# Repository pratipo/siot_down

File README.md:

# siot_down
workshop and installation in barcelona, by adi-fad + hangar

:)

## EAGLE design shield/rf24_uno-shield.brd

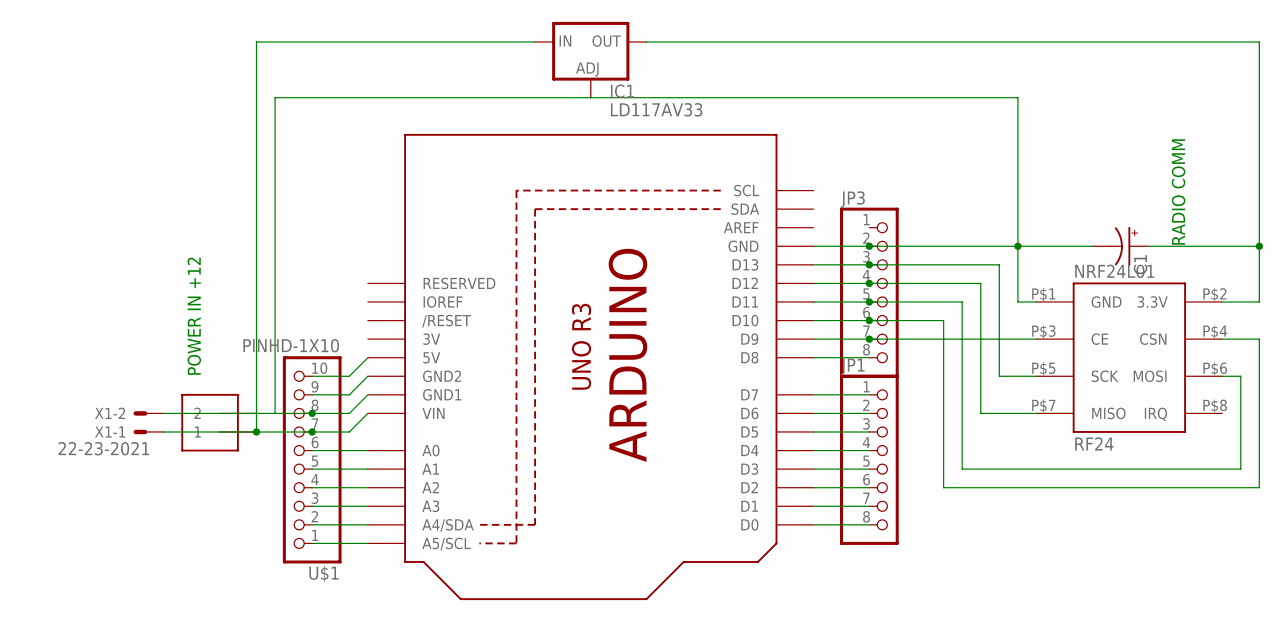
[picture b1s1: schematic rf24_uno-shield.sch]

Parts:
+12V: 1X2-3.5MM
C1: CPOL-USE2-5; E2-5
IC1: LD117AV33; TO220L1
JP1, JP3: PINHD-1X8BIG; 1X08-BIG
NRF24L01: RF24; 4X2HEADER
U1: ARDUINOR3-DIMENSION; ARDUINOR3
U$1: PINHD-1X10; 1X10-BIG
X1: 22-23-2021

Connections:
3V: U1.3V
unnamed: U1.A0, U$1.6
unnamed: C1.+, IC1.2 (OUT), NRF24L01.P$2 (3.3V)
unnamed: +12V.2, C1.-, IC1.1 (ADJ), JP3.2, NRF24L01.P$1 (GND), U1.GND, U1.GND1, U$1.8, X1.2
unnamed: JP3.3, NRF24L01.P$5 (SCK), U1.D13
unnamed: JP3.7, NRF24L01.P$3 (CE), U1.D9
unnamed: JP3.4, NRF24L01.P$7 (MISO), U1.D12
unnamed: JP3.5, NRF24L01.P$6 (MOSI), U1.D11
unnamed: JP3.6, NRF24L01.P$4 (CSN), U1.D10
unnamed: JP1.8, U1.D0
unnamed: U1.A1, U$1.5
unnamed: +12V.1, IC1.3 (IN), U1.VIN, U$1.7, X1.1
unnamed: JP3.8, U1.D8
unnamed: U1.GND2, U$1.9
unnamed: U1.5V, U$1.10
unnamed: U1.A2, U$1.4
unnamed: U1.A3, U$1.3
unnamed: U1.A4 (A4/SDA), U$1.2
unnamed: U1.A5 (A5/SCL), U$1.1
unnamed: JP1.7, U1.D1
unnamed: JP1.6, U1.D2
unnamed: JP1.5, U1.D3
unnamed: JP1.4, U1.D4
unnamed: JP1.3, U1.D5
unnamed: JP1.2, U1.D6
unnamed: JP1.1, U1.D7

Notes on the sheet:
POWER IN +12
RADIO COMM

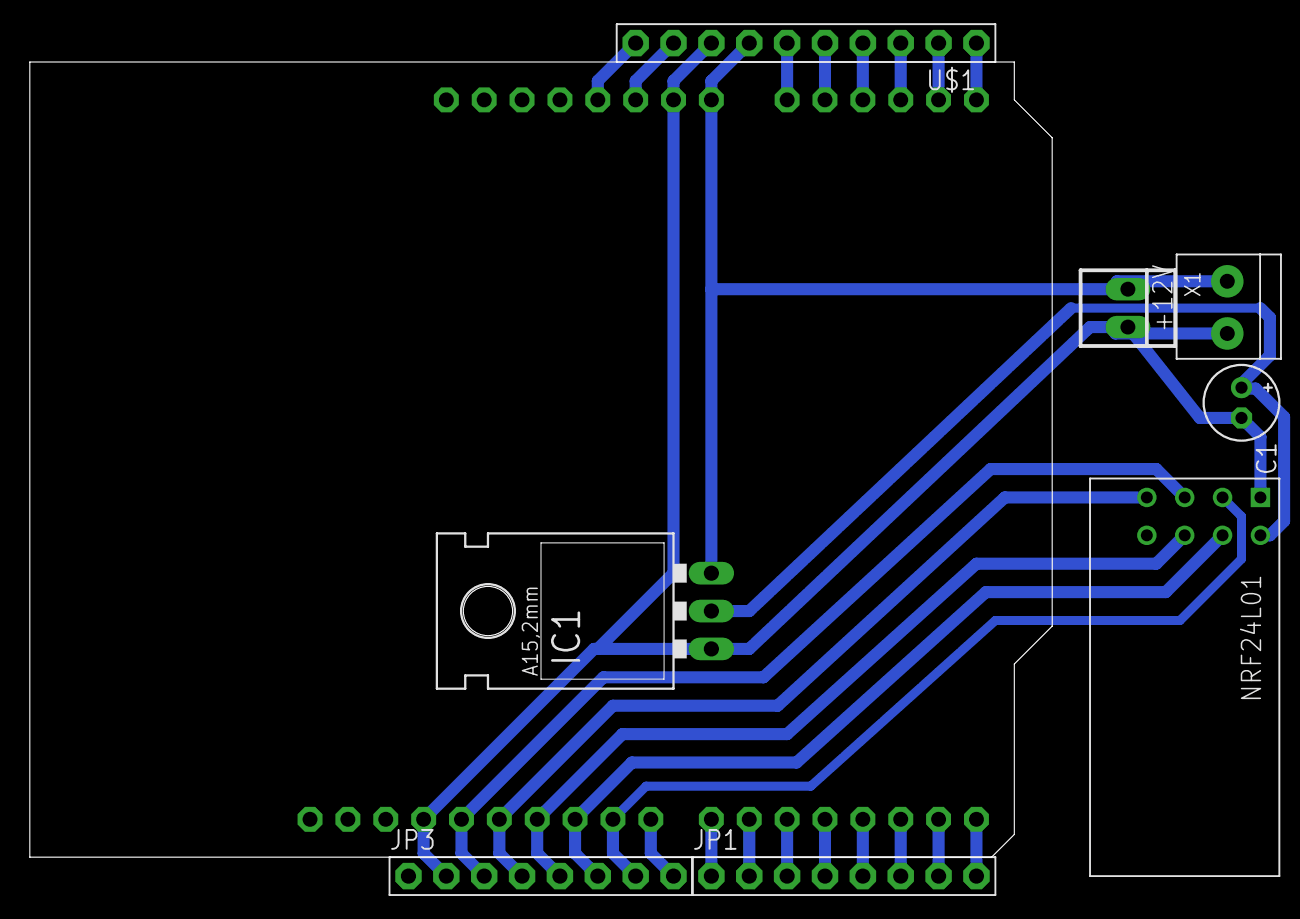
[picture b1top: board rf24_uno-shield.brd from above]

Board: 2 copper layers, 9 parts (1 on the bottom side), 25 nets.

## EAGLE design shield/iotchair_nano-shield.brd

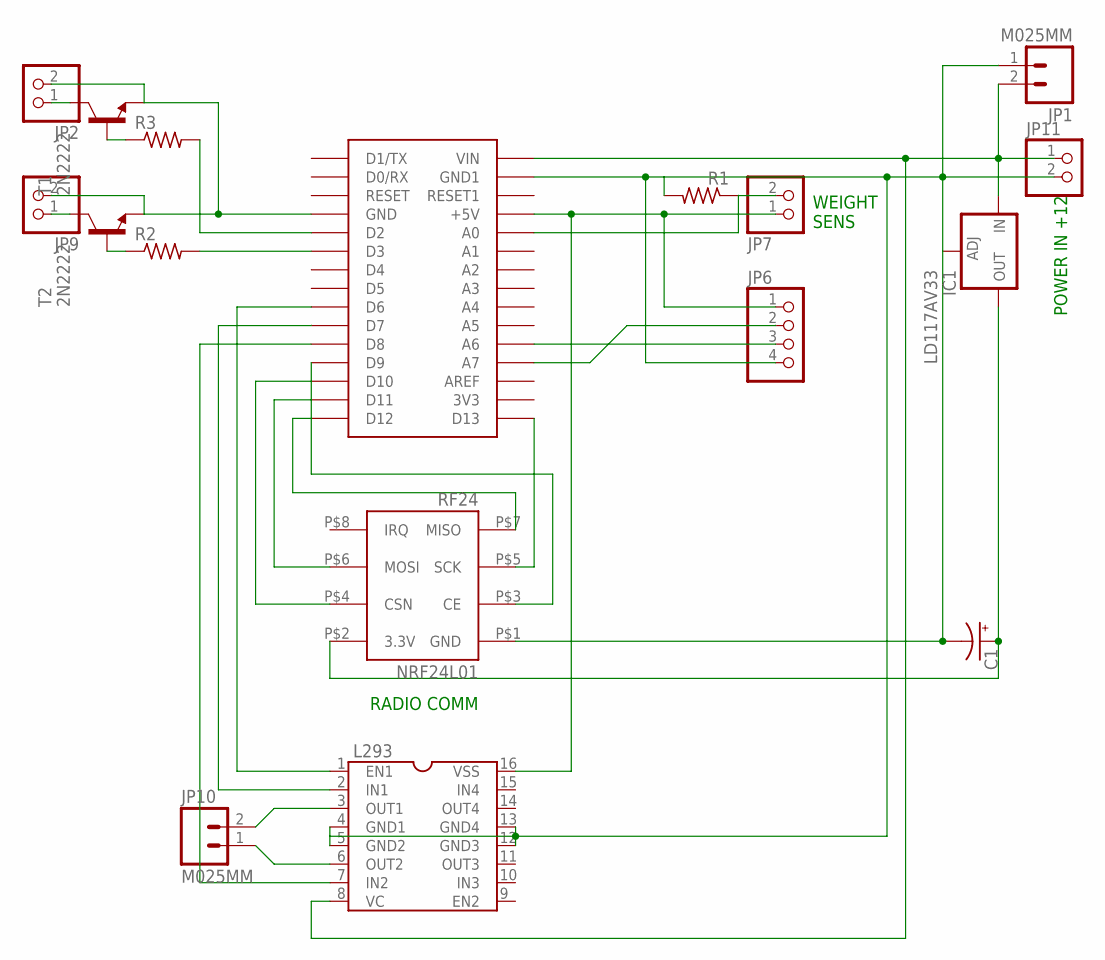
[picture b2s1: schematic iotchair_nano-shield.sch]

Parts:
C1: CPOL-USTT2D6L; TT2D6L
IC1: LD117AV33; TO220L1
JP1, JP10: M025MM; SCREWTERMINAL-5MM-2
JP2, JP7, JP9, JP11: PINHD-1X2; 1X02
JP6: PINHD-1X4; 1X04
L293: DIL16
NRF24L01: RF24; 4X2HEADER
R1, R2, R3: R-US_0204/5; 0204/5
T1, T2: 2N2222; TO92-EBC-OVAL
U$1: ARDUINONANO; PDIP-32

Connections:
unnamed: L293.2 (IN1), U$1.D7
unnamed: C1.+, IC1.2 (OUT), NRF24L01.P$2 (3.3V)
unnamed: JP9.1, T2.C
unnamed: JP6.3, U$1.A6
unnamed: JP7.2, R1.1, U$1.A0
unnamed: IC1.3 (IN), JP1.2, JP11.1, L293.8 (VC), U$1.VIN
unnamed: JP6.2, U$1.A7
unnamed: JP10.1, L293.6 (OUT2)
unnamed: NRF24L01.P$5 (SCK), U$1.D13
unnamed: NRF24L01.P$7 (MISO), U$1.D12
unnamed: NRF24L01.P$6 (MOSI), U$1.D11
unnamed: NRF24L01.P$4 (CSN), U$1.D10
unnamed: NRF24L01.P$3 (CE), U$1.D9
unnamed: L293.1 (EN1), U$1.D6
unnamed: C1.-, IC1.1 (ADJ), JP1.1, JP6.4, JP11.2, L293.4 (GND1), L293.5 (GND2), L293.12 (GND3), L293.13 (GND4), NRF24L01.P$1 (GND), R1.2, U$1.GND1
unnamed: R2.2, U$1.D3
unnamed: L293.7 (IN2), U$1.D8
unnamed: R3.1, T1.B
unnamed: JP2.1, T1.C
unnamed: JP2.2, JP9.2, T1.E, T2.E, U$1.GND
unnamed: R3.2, U$1.D2
unnamed: JP6.1, JP7.1, L293.16 (VSS), U$1.+5V
unnamed: R2.1, T2.B
unnamed: JP10.2, L293.3 (OUT1)

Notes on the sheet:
POWER IN +12
RADIO COMM
WEIGHT SENS

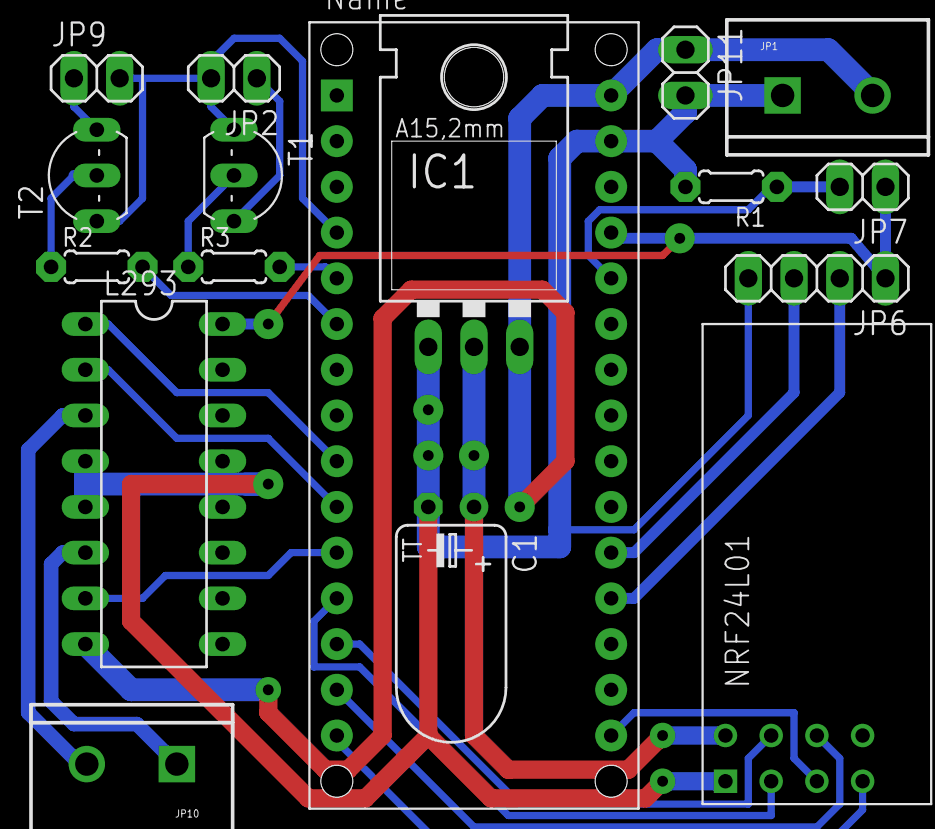
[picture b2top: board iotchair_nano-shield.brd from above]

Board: 2 copper layers, 17 parts (0 on the bottom side), 24 nets.

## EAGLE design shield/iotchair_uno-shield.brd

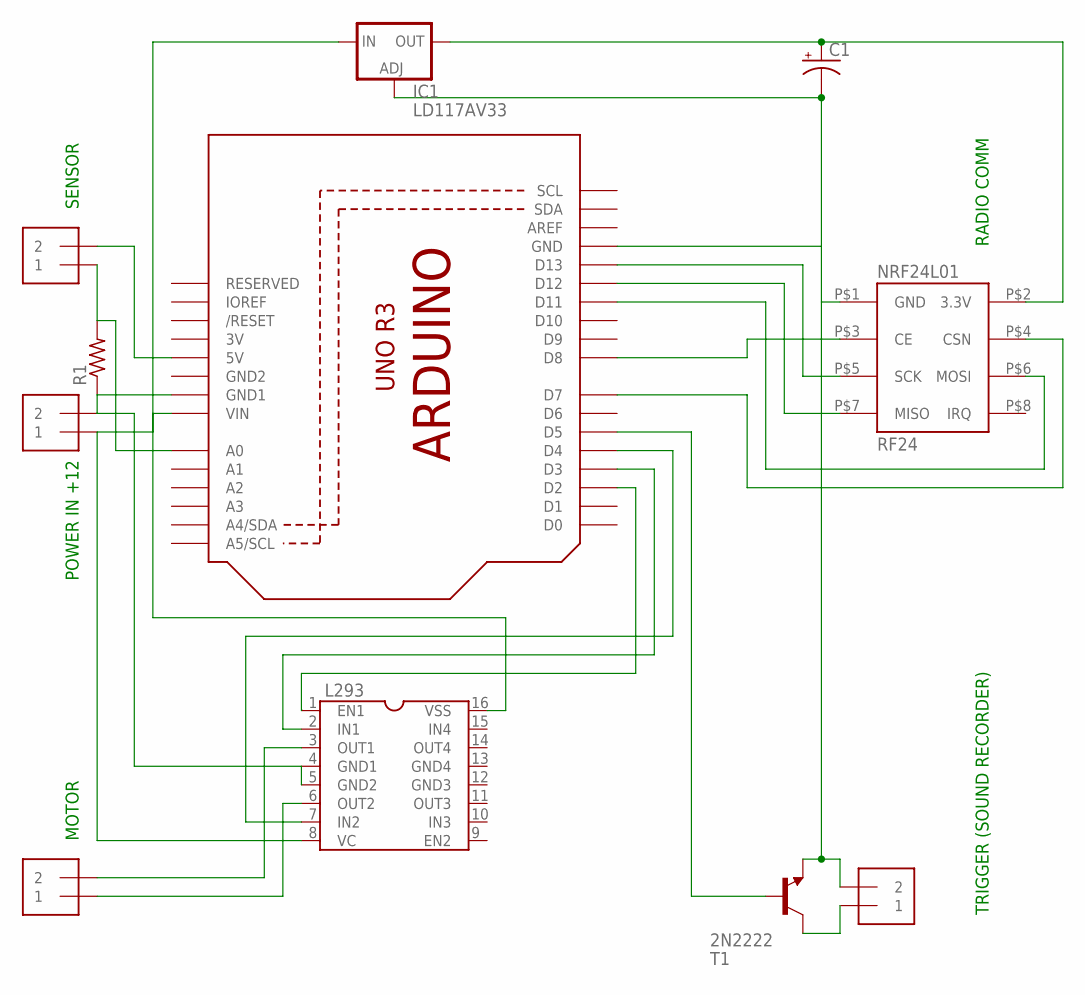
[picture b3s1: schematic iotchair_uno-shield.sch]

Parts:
+12V: 1X2-3.5MM
A_SENS: 1X2-3.5MM
C1: CPOL-USE2-5; E2-5
IC1: LD117AV33; TO220L1
L293: DIL16
MOTOR: 1X2-3.5MM
NRF24L01: RF24; 4X2HEADER
R1: R-US_0207/10; 0207/10
T1: 2N2222; TO92-EBC-OVAL
TRIGGER: 1X2-3.5MM
U1: ARDUINOR3-DIMENSION; ARDUINOR3

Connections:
3V: U1.3V
GND2: U1.GND2
unnamed: A_SENS.2, IC1.3 (IN), L293.16 (VSS), U1.5V
unnamed: C1.+, IC1.2 (OUT), NRF24L01.P$2 (3.3V)
unnamed: C1.-, IC1.1 (ADJ), NRF24L01.P$1 (GND), T1.E, TRIGGER.2, U1.GND
unnamed: NRF24L01.P$5 (SCK), U1.D13
unnamed: NRF24L01.P$3 (CE), U1.D8
unnamed: NRF24L01.P$7 (MISO), U1.D12
unnamed: NRF24L01.P$6 (MOSI), U1.D11
unnamed: NRF24L01.P$4 (CSN), U1.D7
unnamed: A_SENS.1, R1.2, U1.A0
unnamed: L293.6 (OUT2), MOTOR.1
unnamed: +12V.2, L293.4 (GND1), L293.5 (GND2), R1.1, U1.GND1
unnamed: +12V.1, L293.8 (VC), U1.VIN
unnamed: L293.3 (OUT1), MOTOR.2
unnamed: L293.1 (EN1), U1.D2
unnamed: L293.2 (IN1), U1.D3
unnamed: L293.7 (IN2), U1.D4
unnamed: T1.C, TRIGGER.1
unnamed: T1.B, U1.D5

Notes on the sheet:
MOTOR
POWER IN +12
SENSOR
RADIO COMM
TRIGGER (SOUND RECORDER)

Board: 2 copper layers, 11 parts (1 on the bottom side), 18 nets, no tracks yet.

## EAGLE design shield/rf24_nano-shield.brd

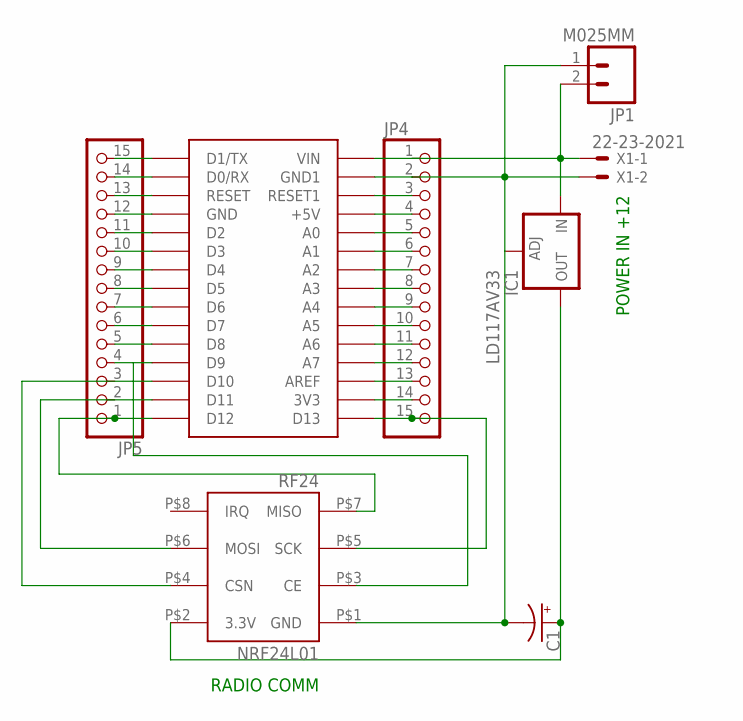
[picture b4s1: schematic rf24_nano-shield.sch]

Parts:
C1: CPOL-USTT2D5; TT2D5
IC1: LD117AV33; TO220L1
JP1: M025MM; SCREWTERMINAL-5MM-2
JP4, JP5: PINHD-1X15; 1X15
NRF24L01: RF24; 4X2HEADER
U$1: ARDUINONANO; PDIP-32
X1: 22-23-2021

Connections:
unnamed: C1.-, IC1.1 (ADJ), JP1.1, JP4.2, NRF24L01.P$1 (GND), U$1.GND1, X1.2
unnamed: C1.+, IC1.2 (OUT), NRF24L01.P$2 (3.3V)
unnamed: JP5.13, U$1.RESET
unnamed: JP4.3, U$1.RESET1
unnamed: IC1.3 (IN), JP1.2, JP4.1, U$1.VIN, X1.1
unnamed: JP4.4, U$1.+5V
unnamed: JP4.5, U$1.A0
unnamed: JP4.6, U$1.A1
unnamed: JP4.7, U$1.A2
unnamed: JP4.8, U$1.A3
unnamed: JP4.9, U$1.A4
unnamed: JP4.10, U$1.A5
unnamed: JP4.11, U$1.A6
unnamed: JP4.12, U$1.A7
unnamed: JP4.13, U$1.AREF
unnamed: JP4.14, U$1.3V3
unnamed: JP4.15, NRF24L01.P$5 (SCK), U$1.D13
unnamed: JP5.1, NRF24L01.P$7 (MISO), U$1.D12
unnamed: NRF24L01.P$6 (MOSI), U$1.D11
unnamed: NRF24L01.P$4 (CSN), U$1.D10
unnamed: JP5.4, NRF24L01.P$3 (CE), U$1.D9
unnamed: JP5.5, U$1.D8
unnamed: JP5.6, U$1.D7
unnamed: JP5.7, U$1.D6
unnamed: JP5.8, U$1.D5
unnamed: JP5.9, U$1.D4
unnamed: JP5.10, U$1.D3
unnamed: JP5.11, U$1.D2
unnamed: JP5.12, U$1.GND
unnamed: JP5.14, U$1.D0/RX
unnamed: JP5.15, U$1.D1/TX

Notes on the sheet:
POWER IN +12
RADIO COMM

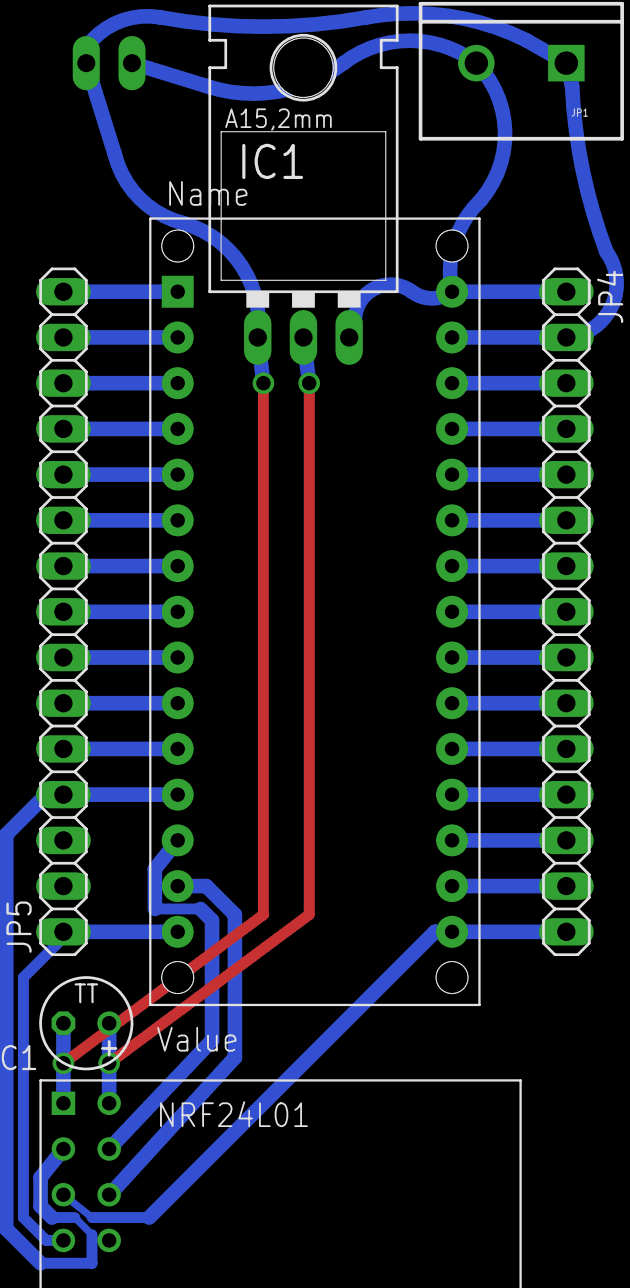
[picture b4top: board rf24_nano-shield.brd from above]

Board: 2 copper layers, 8 parts (1 on the bottom side), 31 nets.

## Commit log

2015-02-28 up to the git cloud
2015-02-28 added tweting script
2015-03-02 added individual chair behaviour
2017-09-26 smile
    i made the code happier

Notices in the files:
parts and their libraries:
SparkFun-Connectors: Licensing: Creative Commons ShareAlike 4.0 International - https://creativecommons.org/licenses/by-sa/4.0
